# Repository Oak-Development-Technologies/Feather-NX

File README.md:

# Feather-NX
Home of the Feather NX - The First Crosslink-NX based Feather Development Board

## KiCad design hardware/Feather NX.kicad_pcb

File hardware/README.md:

# Hardware Files for Feather NX

Feather NX is a Lattice Semiconductor based FPGA Feather Board using the Crosslink-NX LIFCL-40-7BG256I Crosslink-NX FPGA. The board features an FT232H to operate as a JTAG host in which you can program the FPGA bitstream. 

No high speed SERDES are broken out.

DPHY0 is broken out completely to a Raspberry Pi 22 Pin compatible 4 lane MIPI FPC connector. Due to manufacturing constraints and costs, manufacturing on a standard 6L service from JLCPCB will only yield between 64 and 67 ohms of
differential impedance, or around 32 ohms single ended impedance.

Additionally, 4 pairs of differential length matched traces are broken on the longer edge of the board next to the 4 available analog pins on the FPGA. These should have approximate differential impedance of between 64 and 67 ohms.

The remaining pins on the other side are differentially routed but not length matched with similar expected impedance characteristics.

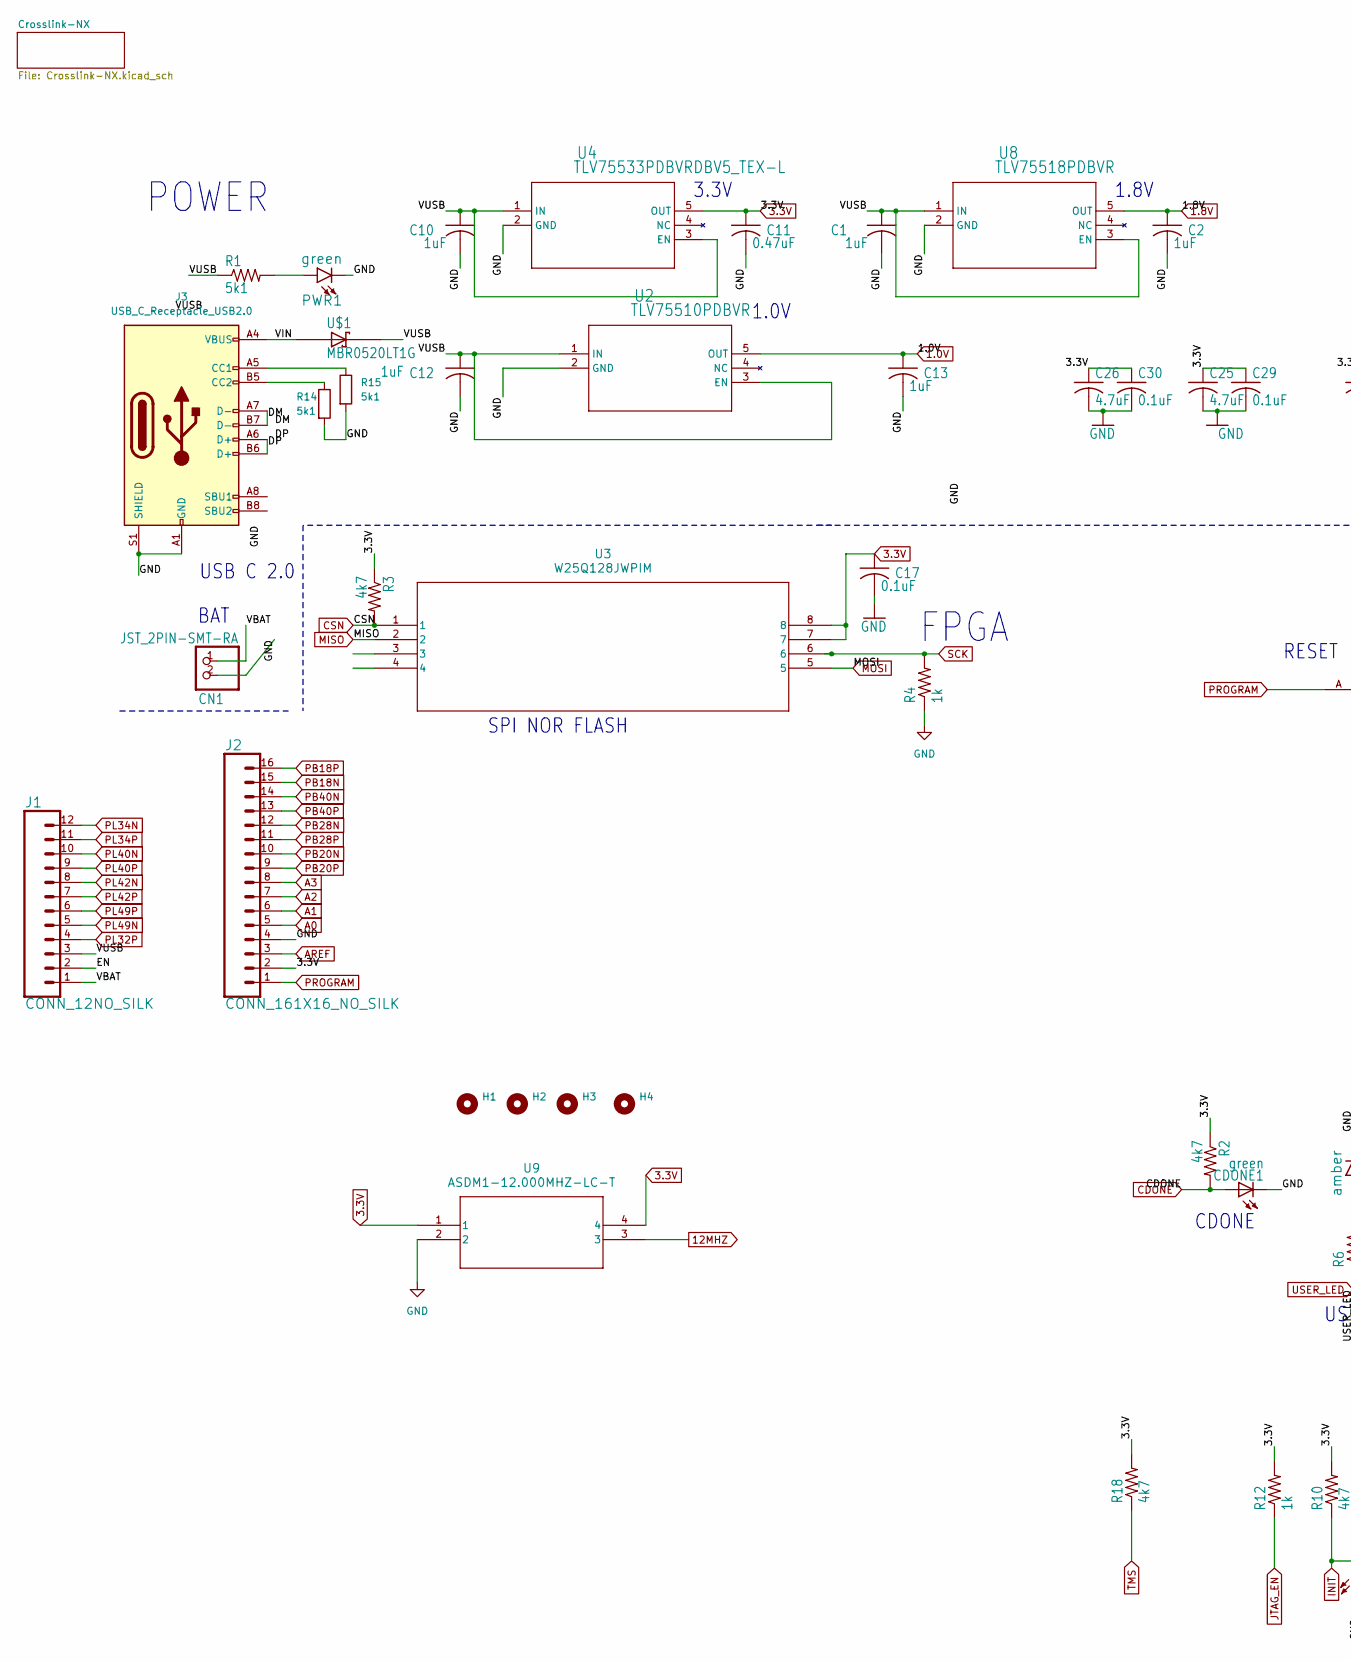
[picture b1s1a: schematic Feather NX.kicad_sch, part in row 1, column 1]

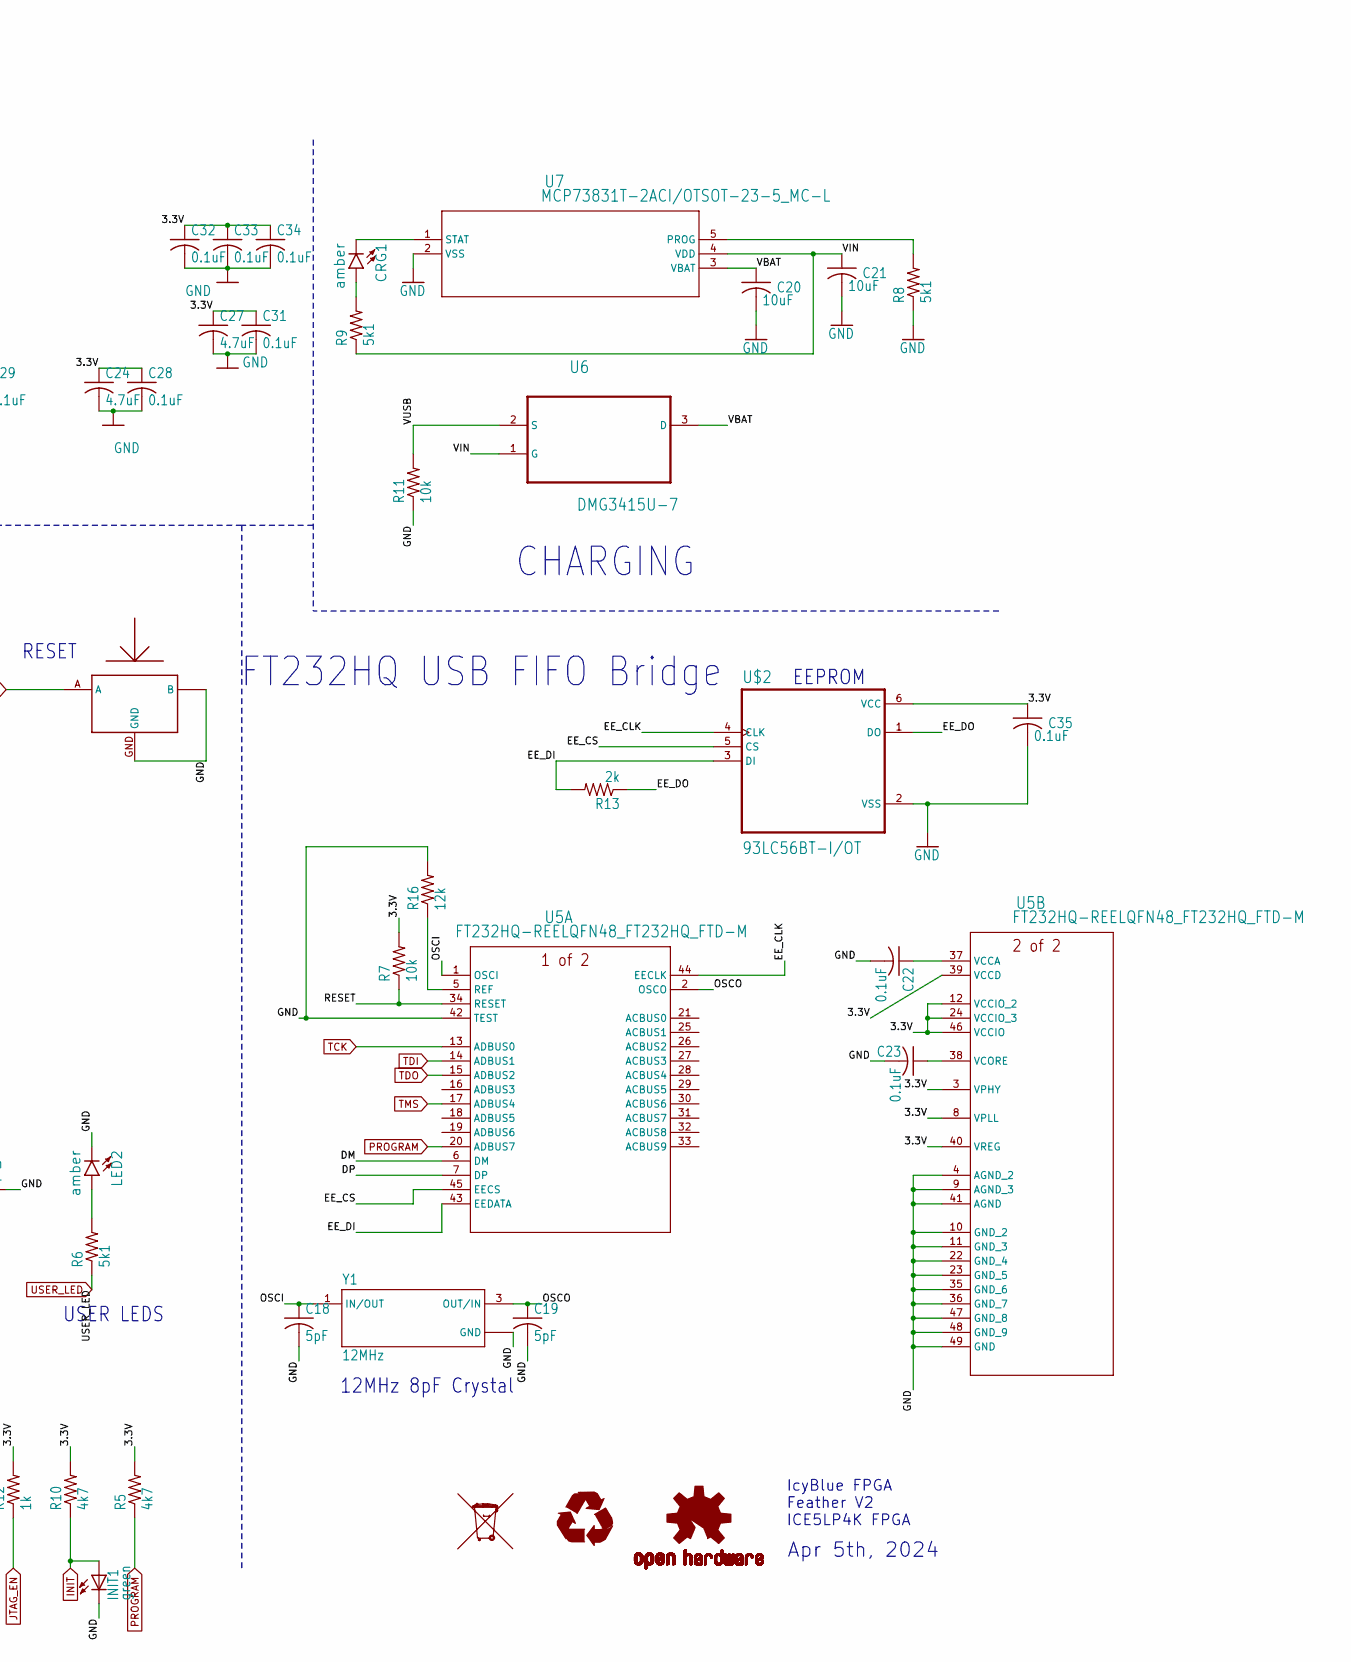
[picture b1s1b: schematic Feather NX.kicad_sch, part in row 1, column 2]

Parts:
C1, C2, C10, C12, C13: 1uF; C_0402_1005Metric
C11: 0.47uF; C_0402_1005Metric
C17, C22, C23, C28, C29, C30, C31, C32, C33, C34, C35: 0.1uF; C_0402_1005Metric
C18, C19: 5pF; C_0402_1005Metric
C20, C21: 10uF; C_0603_1608Metric
C24, C25, C26, C27: 4.7uF; C_0603_1608Metric
CDONE1: green; LED-0603
CN1: JST_2PIN-SMT-RA; JST-PH-2-SMT-RA
CRG1: amber; LED-0603
H1, H2: MountingHole; MountingHole_2.5mm
H3, H4: MountingHole; MountingHole_2.5mm_Pad
INIT1: green; LED-0603
J1: CONN_12NO_SILK; 1X12_NO_SILK
J2: CONN_161X16_NO_SILK; 1X16_NO_SILK
J3: USB_C_Receptacle_USB2.0; USB_C_Receptacle_GCT_USB4105-xx-A_16P_TopMnt_Horizontal
LED2: amber; LED-0603
LOGO1: OSHW-LOGOS; OSHW-LOGO-S
PWR1: green; LED-0603
R1, R6, R8, R9, R14, R15: 5k1; R_0402_1005Metric
R2, R3, R5, R10, R18: 4k7; R_0402_1005Metric
R4, R12: 1k; R_0402_1005Metric
R7, R11: 10k; R_0402_1005Metric
R13: 2k; R0402
R16: 12k; R_0402_1005Metric
U2: TLV75510PDBVR; DBV5_TEX-L
U3: W25Q128JWPIM; W25Q128JW_WSON 6x5-mm_WIN
U4: TLV75533PDBVRDBV5_TEX-L; DBV5_TEX-L
U5: FT232HQ-REELQFN48_FT232HQ_FTD-M; QFN48_FT232HQ_FTD-M
U6: DMG3415U-7; SOT95P240X105-3N
U7: MCP73831T-2ACI/OTSOT-23-5_MC-L; SOT-23-5_MC-L
U8: TLV75518PDBVR; DBV5_TEX-L
U9: ASDM1-12.000MHZ-LC-T; ASDM1-12.000MHZ-LC-T_ABR-L
U$1: MBR0520LT1G; SOD3716X117(SOD-123)
U$2: 93LC56BT-I/OT; SOT95P280X145-6N
U$3: SOF-232HST; 3.3X2.9
Y1: 12MHz; XTAL_ECS-480-10-37-JTN-TR

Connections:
1.0V: C13.1, U2.5 (OUT); also elsewhere on the board
1.8V: C2.1, J2.3, U8.5 (OUT); also elsewhere on the board
3.3V: C11.1, C17.1, C24.1, C25.1, C26.1, C27.1, C28.1, C29.1, C30.1, C31.1, C32.1, C33.1, C34.1, C35.1, J2.2, R2.1, R3.1, R5.2, R7.2, R10.2, R12.2, R18.2, U3.7, U3.8, U4.5 (OUT), U5.3 (VPHY), U5.8 (VPLL), U5.12 (VCCIO_2), U5.24 (VCCIO_3), U5.39 (VCCD), U5.40 (VREG), U5.46 (VCCIO), U9.1, U9.4, U$2.6 (VCC); also elsewhere on the board
12MHZ: U9.3; also elsewhere on the board
/DM: J3.A7 (D-), J3.B7 (D-), U5.6 (DM)
/DP: J3.A6 (D+), J3.B6 (D+), U5.7 (DP)
/EE_CLK: U5.44 (EECLK), U$2.4 (CLK)
/EE_CS: U5.45 (EECS), U$2.5 (CS)
/EE_DI: R13.2, U5.43 (EEDATA), U$2.3 (DI)
/EE_DO: R13.1, U$2.1 (DO)
/EN: J1.2
/OSCI: C18.1, U5.1 (OSCI), Y1.1 (IN/OUT)
/OSCO: C19.1, U5.2 (OSCO), Y1.3 (OUT/IN)
/RESET: R7.1, U5.34 (RESET)
/VBAT: C20.1, CN1.1 (2), J1.1, U6.3 (D), U7.3 (VBAT)
/VIN: C21.1, J3.A4 (VBUS), J3.A9 (VBUS), J3.B4 (VBUS), J3.B9 (VBUS), R9.1, U6.1 (G), U7.4 (VDD), U$1.2 (A)
/VUSB: C1.1, C10.1, C12.1, J1.3, R1.1, R11.2, U2.1 (IN), U2.3 (EN), U4.1 (IN), U4.3 (EN), U6.2 (S), U8.1 (IN), U8.3 (EN), U$1.1 (C)
A0: J2.5; also elsewhere on the board
A1: J2.6; also elsewhere on the board
A2: J2.7; also elsewhere on the board
A3: J2.8; also elsewhere on the board
CDONE: CDONE1.A, R2.2; also elsewhere on the board
CSN: R3.2, U3.1; also elsewhere on the board
GND: C1.2, C2.2, C10.2, C11.2, C12.2, C13.2, C17.2, C18.2, C19.2, C20.2, C21.2, C22.2, C23.2, C24.2, C25.2, C26.2, C27.2, C28.2, C29.2, C30.2, C31.2, C32.2, C33.2, C34.2, C35.2, CDONE1.C, CN1.2 (1), INIT1.C, J2.4, J3.A1 (GND), J3.A12 (GND), J3.B1 (GND), J3.B12 (GND), J3.S1 (SHIELD), LED2.C, PWR1.C, R4.1, R8.1, R11.1, R14.2, R15.2, R16.2, U2.2 (GND), U4.2 (GND), U5.4 (AGND_2), U5.9 (AGND_3), U5.10 (GND_2), U5.11 (GND_3), U5.22 (GND_4), U5.23 (GND_5), U5.35 (GND_6), U5.36 (GND_7), U5.41 (AGND), U5.42 (TEST), U5.47 (GND_8), U5.48 (GND_9), U5.49 (GND), U7.2 (VSS), U8.2 (GND), U9.2, U$2.2 (VSS), U$3.B, U$3.B2 (B), U$3.B3 (B), U$3.GND, Y1.2 (GND), Y1.4 (GND); also elsewhere on the board
INIT: INIT1.A, R10.1; also elsewhere on the board
JTAG_EN: R12.1; also elsewhere on the board
MISO: U3.2; also elsewhere on the board
MOSI: U3.5; also elsewhere on the board
unnamed: CRG1.A, R9.2
unnamed: J3.A5 (CC1), R15.1
unnamed: J3.B5 (CC2), R14.1
unnamed: LED2.A, R6.2
unnamed: PWR1.A, R1.2
unnamed: R16.1, U5.5 (REF)
unnamed: C22.1, U5.37 (VCCA)
unnamed: C23.1, U5.38 (VCORE)
unnamed: R8.2, U7.5 (PROG)
unnamed: CRG1.C, U7.1 (STAT)
PB18N: J2.15; also elsewhere on the board
PB18P: J2.16; also elsewhere on the board
PB20N: J2.10; also elsewhere on the board
PB20P: J2.9; also elsewhere on the board
PB28N: J2.12; also elsewhere on the board
PB28P: J2.11; also elsewhere on the board
PB40N: J2.14; also elsewhere on the board
PB40P: J2.13; also elsewhere on the board
PL32P: J1.4; also elsewhere on the board
PL34N: J1.12; also elsewhere on the board
PL34P: J1.11; also elsewhere on the board
PL40N: J1.10; also elsewhere on the board
PL40P: J1.9; also elsewhere on the board
PL42N: J1.8; also elsewhere on the board
PL42P: J1.7; also elsewhere on the board
PL49N: J1.5; also elsewhere on the board
PL49P: J1.6; also elsewhere on the board
PROGRAM: J2.1, R5.1, U5.20 (ADBUS7), U$3.A; also elsewhere on the board
SCK: R4.2, U3.6; also elsewhere on the board
TCK: U5.13 (ADBUS0); also elsewhere on the board
TDI: U5.14 (ADBUS1); also elsewhere on the board
TDO: U5.15 (ADBUS2); also elsewhere on the board
TMS: R18.1, U5.17 (ADBUS4); also elsewhere on the board
USER_LED: R6.1; also elsewhere on the board

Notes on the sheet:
CHARGING
FPGA
3.3V
SPI NOR FLASH
1.0V
BAT
1.8V
EEPROM
RESET
CDONE
IcyBlue FPGA Feather V2 ICE5LP4K FPGA
USER LEDS
POWER
Apr 5th, 2024
FT232HQ USB FIFO Bridge
12MHz 8pF Crystal
USB C 2.0

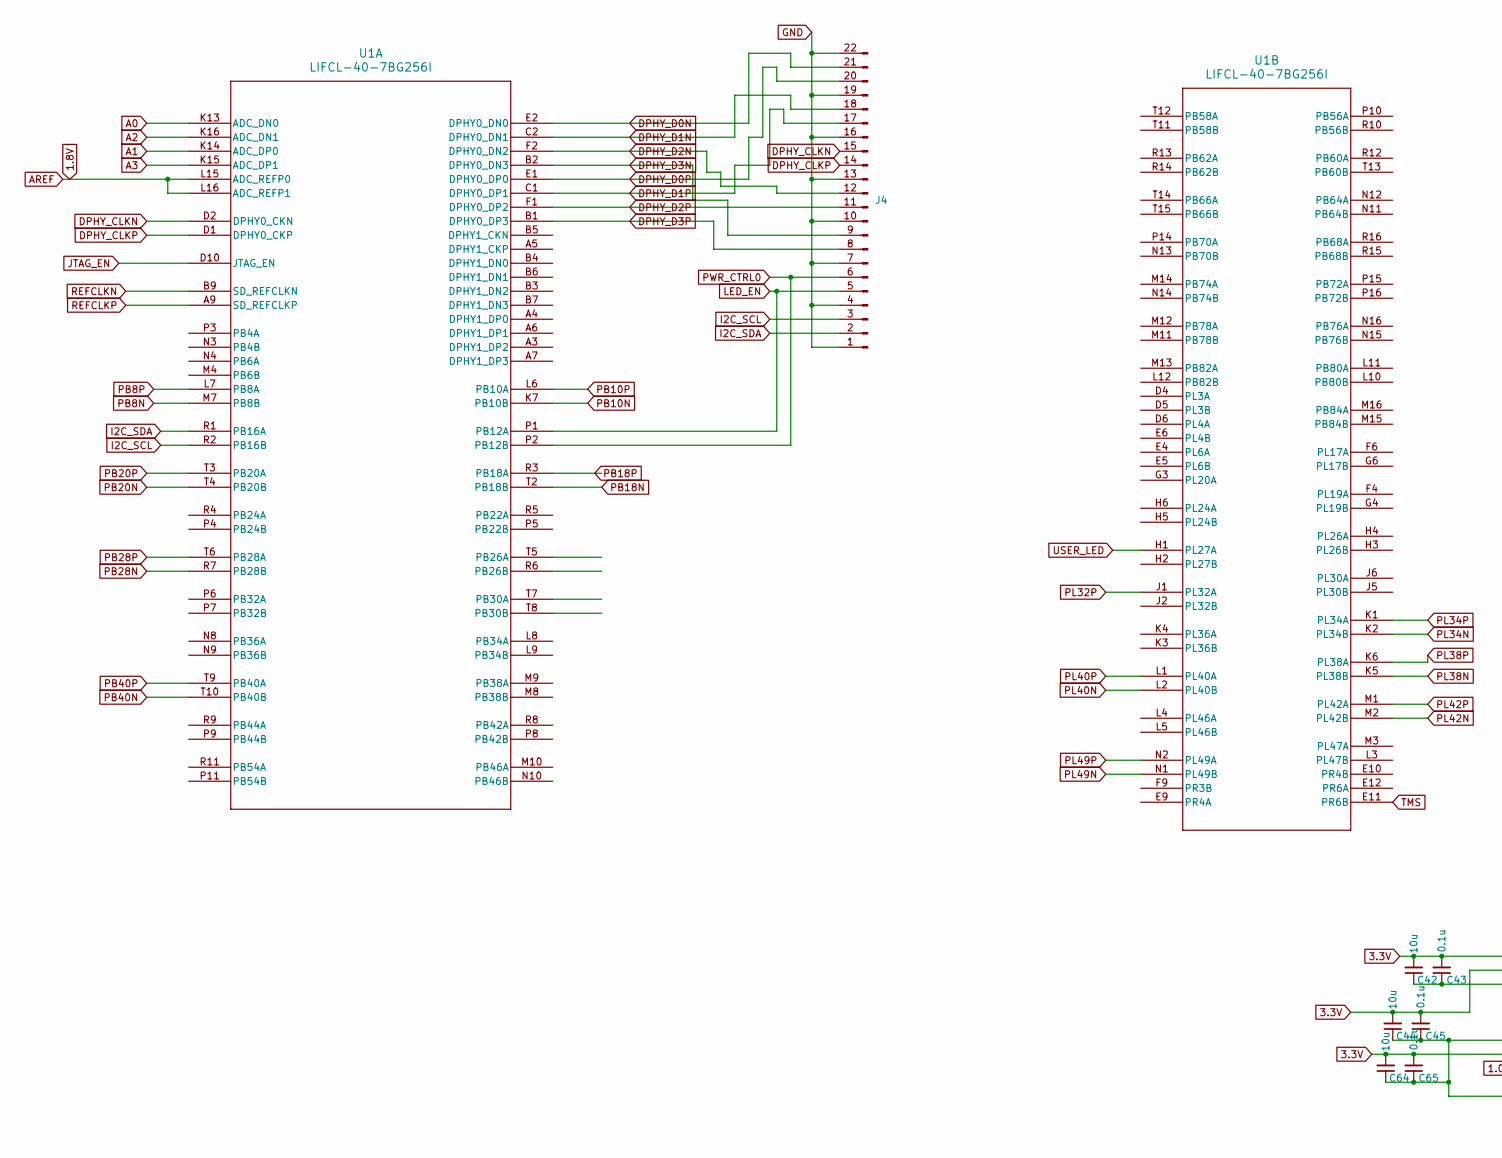
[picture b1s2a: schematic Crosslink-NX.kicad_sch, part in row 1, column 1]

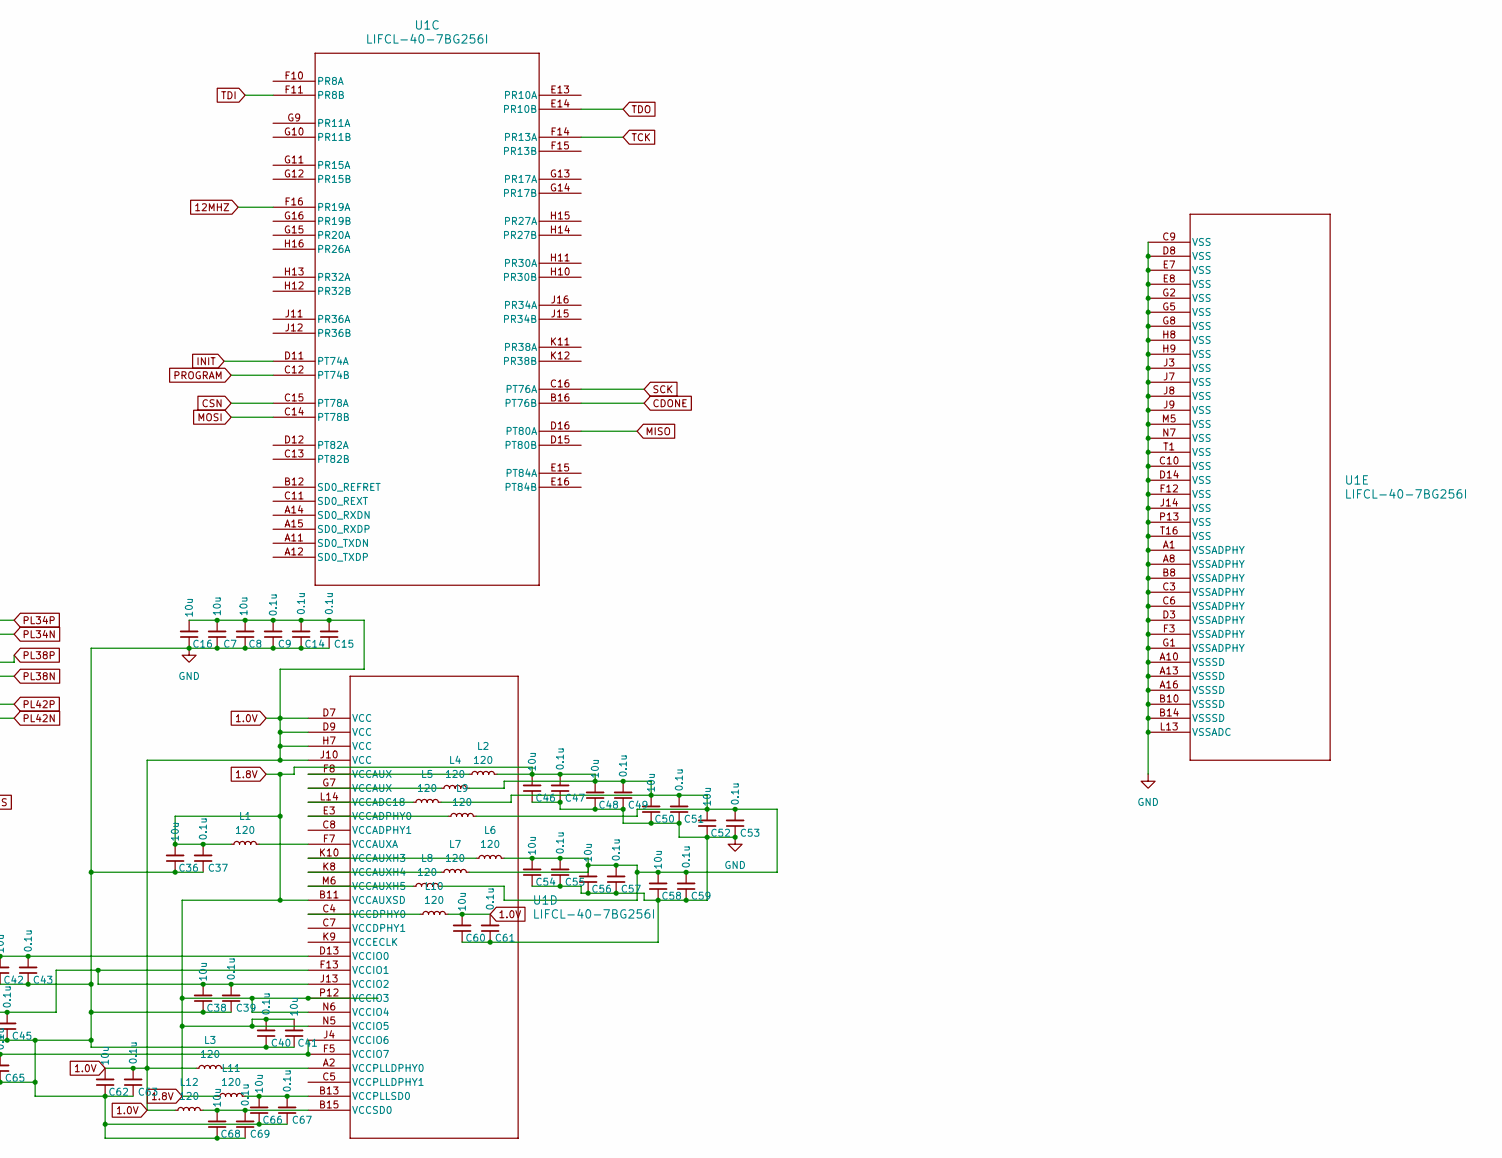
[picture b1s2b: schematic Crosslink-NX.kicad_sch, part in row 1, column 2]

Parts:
C7, C8, C16, C36, C38, C41, C42, C44, C46, C48, C50, C52, C54, C56, C58, C60, C62, C64, C66, C68: 10u; C_0402_1005Metric
C9, C14, C15, C37, C39, C40, C43, C45, C47, C49, C51, C53, C55, C57, C59, C61, C63, C65, C67, C69: 0.1u; C_0201_0603Metric
J4: Hirose_FH12-22S-0.5SH_1x22-1MP_P0.50mm_Horizontal
L1, L2, L3, L4, L5, L6, L7, L8, L9, L10, L11, L12: 120; L_0402_1005Metric
U1: LIFCL-40-7BG256I; caBGA256_LAT

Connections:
1.0V: C7.2, C8.2, C9.2, C14.2, C15.2, C16.2, C60.2, C61.2, C62.2, C63.2, L3.1, L10.2, L12.1, U1.D7 (VCC), U1.D9 (VCC), U1.H7 (VCC), U1.J10 (VCC); also elsewhere on the board
1.8V: C36.2, C37.2, C40.2, C41.2, C46.2, C47.2, C48.2, C49.2, C50.2, C51.2, C52.2, C53.2, C54.2, C55.2, C56.2, C57.2, C58.2, C59.2, L1.1, L2.2, L4.2, L5.2, L6.2, L7.2, L8.2, L9.2, L11.1, U1.B11 (VCCAUXSD), U1.L15 (ADC_REFP0), U1.L16 (ADC_REFP1), U1.N5 (VCCIO5), U1.N6 (VCCIO4), U1.P12 (VCCIO3); also elsewhere on the board
3.3V: C38.2, C39.2, C42.2, C43.2, C44.2, C45.2, C64.2, C65.2, U1.D13 (VCCIO0), U1.F5 (VCCIO7), U1.F13 (VCCIO1), U1.J4 (VCCIO6), U1.J13 (VCCIO2); also elsewhere on the board
12MHZ: U1.F16 (PR19A); also elsewhere on the board
A0: U1.K13 (ADC_DN0); also elsewhere on the board
A1: U1.K14 (ADC_DP0); also elsewhere on the board
A2: U1.K16 (ADC_DN1); also elsewhere on the board
A3: U1.K15 (ADC_DP1); also elsewhere on the board
CDONE: U1.B16 (PT76B); also elsewhere on the board
CSN: U1.C15 (PT78A); also elsewhere on the board
DPHY_CLKN: J4.15, U1.D2 (DPHY0_CKN)
DPHY_CLKP: J4.14, U1.D1 (DPHY0_CKP)
DPHY_D0N: J4.21, U1.E2 (DPHY0_DN0)
DPHY_D0P: J4.20, U1.E1 (DPHY0_DP0)
DPHY_D1N: J4.18, U1.C2 (DPHY0_DN1)
DPHY_D1P: J4.17, U1.C1 (DPHY0_DP1)
DPHY_D2N: J4.12, U1.F2 (DPHY0_DN2)
DPHY_D2P: J4.11, U1.F1 (DPHY0_DP2)
DPHY_D3N: J4.9, U1.B2 (DPHY0_DN3)
DPHY_D3P: J4.8, U1.B1 (DPHY0_DP3)
GND: C7.1, C8.1, C9.1, C14.1, C15.1, C16.1, C36.1, C37.1, C38.1, C39.1, C40.1, C41.1, C42.1, C43.1, C44.1, C45.1, C46.1, C47.1, C48.1, C49.1, C50.1, C51.1, C52.1, C53.1, C54.1, C55.1, C56.1, C57.1, C58.1, C59.1, C60.1, C61.1, C62.1, C63.1, C64.1, C65.1, C66.1, C67.1, C68.1, C69.1, J4.1, J4.4, J4.7, J4.10, J4.13, J4.16, J4.19, J4.22, U1.A1 (VSSADPHY), U1.A8 (VSSADPHY), U1.A10 (VSSSD), U1.A13 (VSSSD), U1.A16 (VSSSD), U1.B8 (VSSADPHY), U1.B10 (VSSSD), U1.B14 (VSSSD), U1.C3 (VSSADPHY), U1.C6 (VSSADPHY), U1.C9 (VSS), U1.C10 (VSS), U1.D3 (VSSADPHY), U1.D8 (VSS), U1.D14 (VSS), U1.E7 (VSS), U1.E8 (VSS), U1.F3 (VSSADPHY), U1.F12 (VSS), U1.G1 (VSSADPHY), U1.G2 (VSS), U1.G5 (VSS), U1.G8 (VSS), U1.H8 (VSS), U1.H9 (VSS), U1.J3 (VSS), U1.J7 (VSS), U1.J8 (VSS), U1.J9 (VSS), U1.J14 (VSS), U1.L13 (VSSADC), U1.M5 (VSS), U1.N7 (VSS), U1.P13 (VSS), U1.T1 (VSS), U1.T16 (VSS); also elsewhere on the board
I2C_SCL: J4.3, U1.R2 (PB16B)
I2C_SDA: J4.2, U1.R1 (PB16A)
INIT: U1.D11 (PT74A); also elsewhere on the board
JTAG_EN: U1.D10 (JTAG_EN); also elsewhere on the board
LED_EN: J4.5, U1.P1 (PB12A)
MISO: U1.D16 (PT80A); also elsewhere on the board
MOSI: U1.C14 (PT78B); also elsewhere on the board
unnamed: L2.1, U1.F8 (VCCAUX)
unnamed: L4.1, U1.G7 (VCCAUX)
unnamed: L5.1, U1.L14 (VCCADC18)
unnamed: L9.1, U1.E3 (VCCADPHY0)
unnamed: L1.2, U1.F7 (VCCAUXA)
unnamed: L6.1, U1.K10 (VCCAUXH3)
unnamed: L7.1, U1.K8 (VCCAUXH4)
unnamed: L8.1, U1.M6 (VCCAUXH5)
unnamed: L10.1, U1.C4 (VCCDPHY0)
unnamed: L3.2, U1.A2 (VCCPLLDPHY0)
unnamed: C66.2, C67.2, L11.2, U1.B13 (VCCPLLSD0)
unnamed: C68.2, C69.2, L12.2, U1.B15 (VCCSD0)
PB8N: U1.M7 (PB8B)
PB8P: U1.L7 (PB8A)
PB10N: U1.K7 (PB10B)
PB10P: U1.L6 (PB10A)
PB18N: U1.T2 (PB18B); also elsewhere on the board
PB18P: U1.R3 (PB18A); also elsewhere on the board
PB20N: U1.T4 (PB20B); also elsewhere on the board
PB20P: U1.T3 (PB20A); also elsewhere on the board
PB28N: U1.R7 (PB28B); also elsewhere on the board
PB28P: U1.T6 (PB28A); also elsewhere on the board
PB40N: U1.T10 (PB40B); also elsewhere on the board
PB40P: U1.T9 (PB40A); also elsewhere on the board
PL32P: U1.J1 (PL32A); also elsewhere on the board
PL34N: U1.K2 (PL34B); also elsewhere on the board
PL34P: U1.K1 (PL34A); also elsewhere on the board
PL38N: U1.K5 (PL38B)
PL38P: U1.K6 (PL38A)
PL40N: U1.L2 (PL40B); also elsewhere on the board
PL40P: U1.L1 (PL40A); also elsewhere on the board
PL42N: U1.M2 (PL42B); also elsewhere on the board
PL42P: U1.M1 (PL42A); also elsewhere on the board
PL49N: U1.N1 (PL49B); also elsewhere on the board
PL49P: U1.N2 (PL49A); also elsewhere on the board
PROGRAM: U1.C12 (PT74B); also elsewhere on the board
PWR_CTRL0: J4.6, U1.P2 (PB12B)
REFCLKN: U1.B9 (SD_REFCLKN)
REFCLKP: U1.A9 (SD_REFCLKP)
SCK: U1.C16 (PT76A); also elsewhere on the board
TCK: U1.F14 (PR13A); also elsewhere on the board
TDI: U1.F11 (PR8B); also elsewhere on the board
TDO: U1.E14 (PR10B); also elsewhere on the board
TMS: U1.E11 (PR6B); also elsewhere on the board
USER_LED: U1.H1 (PL27A); also elsewhere on the board

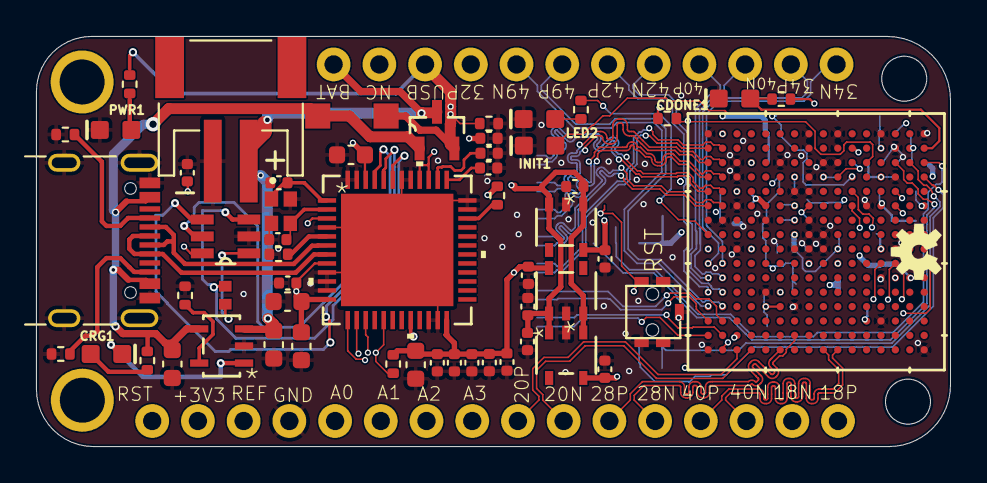
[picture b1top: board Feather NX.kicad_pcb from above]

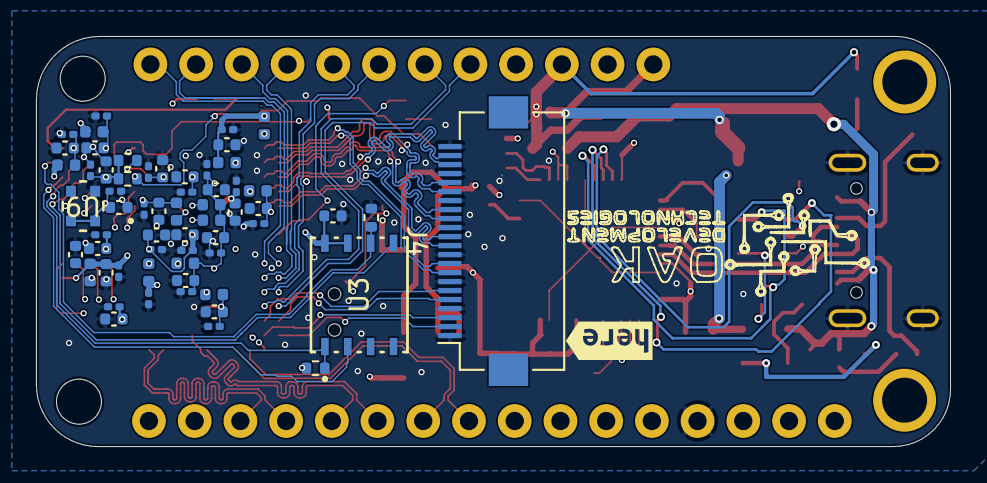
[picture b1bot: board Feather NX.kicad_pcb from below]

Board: 6 copper layers, 50.8 x 22.8 mm, 123 parts (61 on the bottom side), 87 nets.

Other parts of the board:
kibuzzard-665CF276: G***; kibuzzard-665CF276

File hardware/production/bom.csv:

Designator,Footprint,Quantity,Value,LCSC Part #
"C1, C10, C12, C13, C2",0402,5,1uF,
C11,0402,1,0.47uF,
"C14, C15, C37, C39, C40, C43, C45, C47, C49, C51, C53, C55, C57, C59, C61, C63, C65, C67, C69, C9",0201,20,0.1u,
"C16, C36, C38, C41, C42, C44, C46, C48, C50, C52, C54, C56, C58, C60, C62, C64, C66, C68, C7, C8",0402,20,10u,
"C17, C22, C23, C28, C29, C30, C31, C32, C33, C34, C35",0402,11,0.1uF,
"C18, C19",0402,2,5pF,
"C20, C21",0603,2,10uF,
"C24, C25, C26, C27",0603,4,4.7uF,
"CDONE1, INIT1, PWR1",LED-0603,3,green,
CN1,JST-PH-2-SMT-RA,1,JST_2PIN-SMT-RA,
"CRG1, LED2",LED-0603,2,amber,
"H1, H2",MountingHole_2.5mm,2,MountingHole,
"H3, H4",MountingHole_2.5mm_Pad,2,MountingHole,
J1,1X12_NO_SILK,1,CONN_12NO_SILK,
J2,1X16_NO_SILK,1,CONN_161X16_NO_SILK,
J3,USB_C_Receptacle_GCT_USB4105-xx-A_16P_TopMnt_Horizontal,1,USB_C_Receptacle_USB2.0,
J4,Hirose_FH12-22S-0.5SH_1x22-1MP_P0.50mm_Horizontal,1,~,
"L1, L10, L11, L12, L2, L3, L4, L5, L6, L7, L8, L9",0402,12,120,
LOGO1,OSHW-LOGO-S,1,OSHW-LOGOS,
"R1, R14, R15, R6, R8, R9",0402,6,5k1,
"R10, R18, R2, R3, R5",0402,5,4k7,
"R11, R7",0402,2,10k,
"R12, R4",0402,2,1k,
R13,R0402,1,2k,
R16,0402,1,12k,
U$1,SOD3716X117(SOD-123),1,MBR0520LT1G,
U$2,SOT95P280X145-6N,1,93LC56BT-I/OT,
U$3,3.3X2.9,1,SOF-232HST,
U1,caBGA256_LAT,1,LIFCL-40-7BG256I,
U2,DBV5_TEX-L,1,TLV75510PDBVR,
U3,W25Q128JW_WSON 6x5-mm_WIN,1,W25Q128JWPIM,
U4,DBV5_TEX-L,1,TLV75533PDBVRDBV5_TEX-L,
U5,QFN48_FT232HQ_FTD-M,1,FT232HQ-REELQFN48_FT232HQ_FTD-M,
U6,SOT95P240X105-3N,1,DMG3415U-7,
U7,SOT-23-5_MC-L,1,MCP73831T-2ACI/OTSOT-23-5_MC-L,
U8,DBV5_TEX-L,1,TLV75518PDBVR,
U9,ASDM1-12.000MHZ-LC-T_ABR-L,1,ASDM1-12.000MHZ-LC-T,
Y1,XTAL_ECS-480-10-37-JTN-TR,1,12MHz,
